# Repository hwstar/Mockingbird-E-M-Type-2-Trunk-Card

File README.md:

# Mockingbird-E-M-Type-2-Trunk-Card
An E&amp;M Type 2 trunk card for the Mockingbird Telephone Exchange

An interface card design for the Mockingbird Telephone Exchange. 

Features: 
* Provides one E&M type 2 interface
* STM32F103C8T6 microcontroller.
* Isolated local -48VDC supply for the M lead current
* Dry contacts for the E-lead
* Separate  RJ45 jacks for signalling and trunk pinouts.
* Uses standard 4 pair EIA568B Network cable pinout.
* Adjustable audio levels
* Accessed from the Main Microcontroller over I2C
* ATTEN signal to main microcontroller to tell it when there is an event to service.
* 4 Wire transformer isolated audio interface converts the balanced interface audio to unbalanced.
* Design in KiCAD 8.0.

The main project website is on hackaday.io here: https://hackaday.io/project/196044-mockingbird-telephone-exchange

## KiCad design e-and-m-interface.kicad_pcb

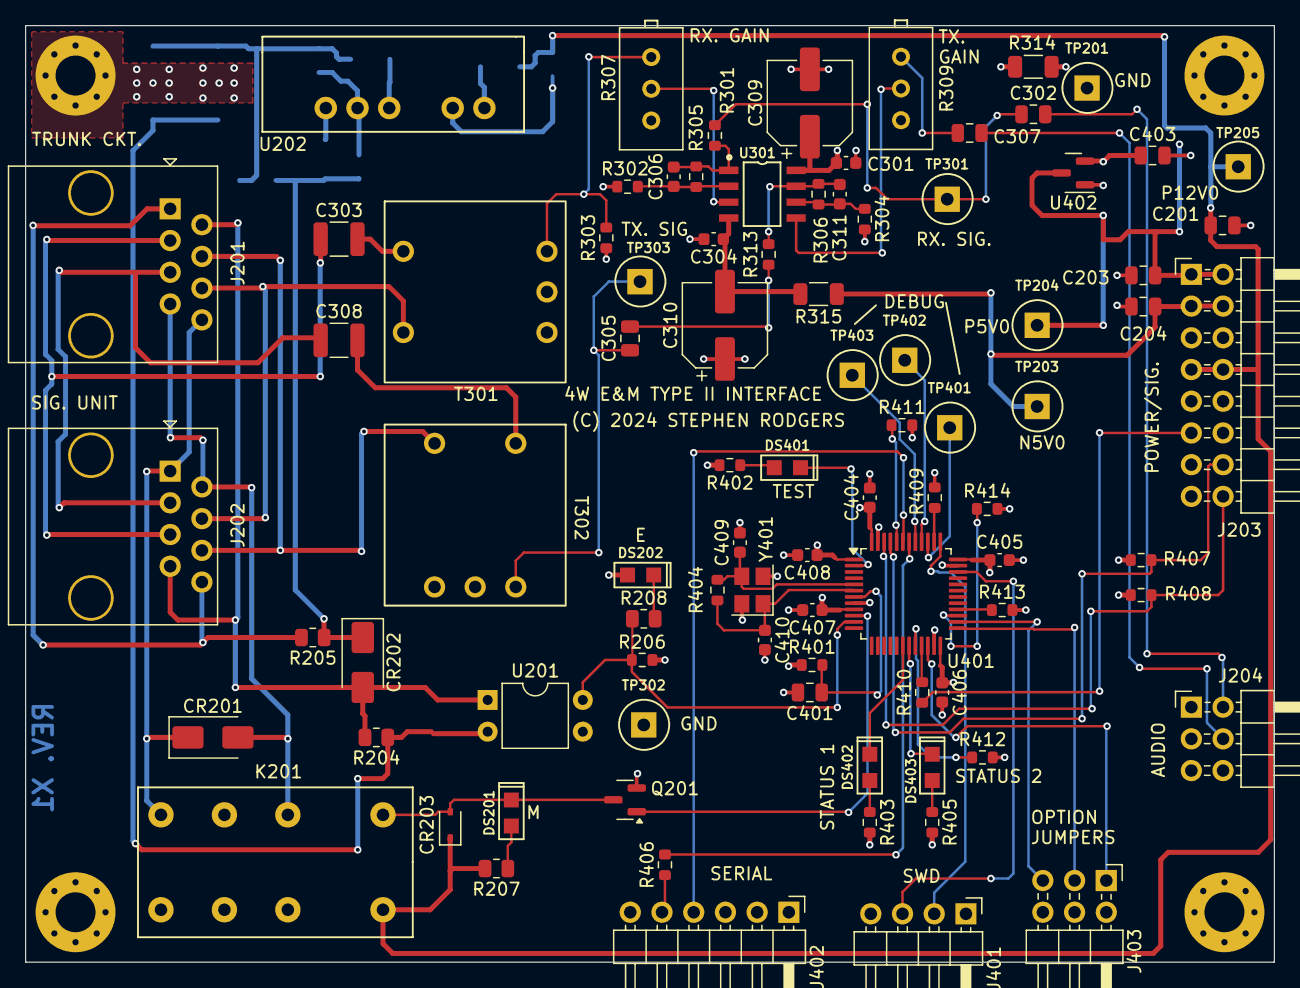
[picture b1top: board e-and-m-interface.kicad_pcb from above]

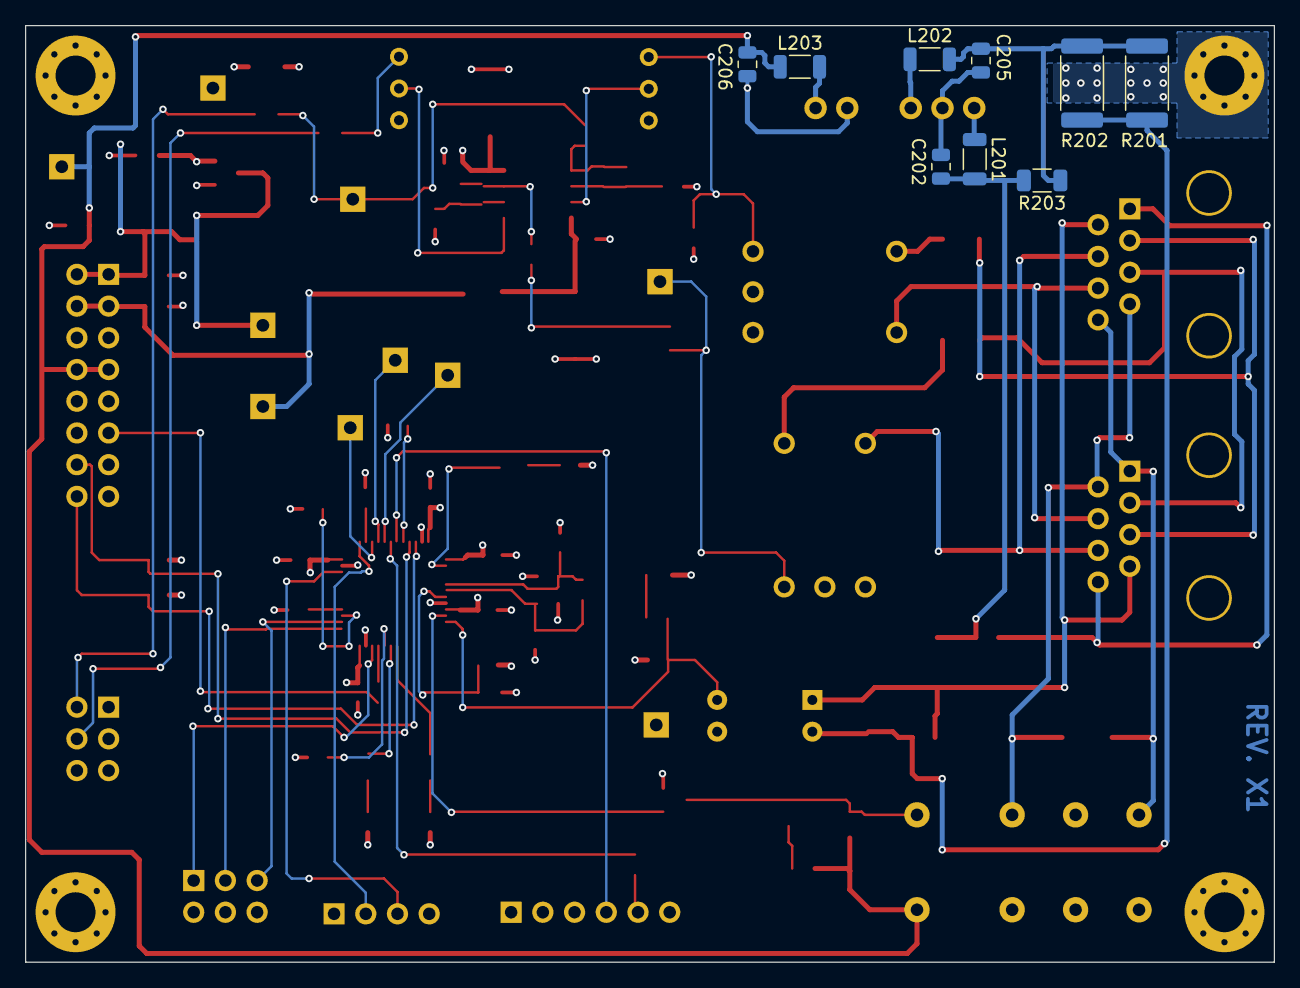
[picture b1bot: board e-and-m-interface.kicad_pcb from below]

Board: 4 copper layers, 100.0 x 75.0 mm, 101 parts (9 on the bottom side), 71 nets.

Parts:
C201, C203, C204: 10u; C_0805_2012Metric
C202, C205: 0.47u; C_0805_2012Metric
C206: 4.7u; C_0805_2012Metric
C301, C304, C404, C405, C406, C407, C408: 0.1u; C_0603_1608Metric
C302, C305, C307: 10U; C_0805_2012Metric
C303, C308: 3.3u; C_1210_3225Metric
C306, C311: 33p; C_0603_1608Metric
C309, C310: 100U; CP_Elec_6.3x7.7
C401: 1u; C_0805_2012Metric
C403: 22u; C_0805_2012Metric
C409, C410: 22p; C_0603_1608Metric
CR201, CR202: SMAJ64CA; D_SMA
CR203: 1N4148WS; D_SOD-323
DS201, DS202, DS401, DS402, DS403: LEDGRN-SAR; LED0805
J201, J202: RJ45; CONN_RJ45_HCTL_HC_RJ45_058_1_6
J203: Conn_02x08_Odd_Even; PinHeader_2x08_P2.54mm_Horizontal
J204, J403: Conn_02x03_Odd_Even; PinHeader_2x03_P2.54mm_Horizontal
J401: CONN4; PinHeader_1x04_P2.54mm_Horizontal
J402: CONN6; PinHeader_1x06_P2.54mm_Horizontal
K201: RELAY_2RT; RELAY-DPDT-HRS2H
L201, L202, L203: 4.7uH; L_1206_3216Metric
MH201, MH202, MH203, MH204: MountingHole_Pad; MountingHole_3.2mm_M3_Pad_Via
Q201: 2N7002; SOT-23
R201, R202: 4.7K; R_2512_6332Metric
R203: 12K; R_1206_3216Metric
R204, R208: 180; R_0805_2012Metric
R205: 0; R_0805_2012Metric
R206: 4.7K; R_0603_1608Metric
R207: 470; R_0805_2012Metric
R301, R410: 33; R_0603_1608Metric
R302, R304: 22K; R_0603_1608Metric
R303, R313: 620; R_0603_1608Metric
R305, R306: 100K; R_0603_1608Metric
R307, R309: 10K; Potentiometer_Bourns_3296X_Horizontal_Screw_SS
R314, R315: 10; R_1206_3216Metric
R401, R411, R412: 10K; R_0603_1608Metric
R402, R403, R405, R406: 470; R_0603_1608Metric
R404: 1M; R_0603_1608Metric
R407, R408: 2.2K; R_0603_1608Metric
R409, R413, R414: 0; R_0603_1608Metric
T301, T302: XFMR-AUDIO-COUPLING; XFMR_AUDIO_COUPLING_PP3.575_SPC_11_HOLE_0.85
TP201, TP203, TP204, TP205, TP301, TP302, TP303, TP401, TP402, TP403: TESTPINTPSQ025; TESTPIN
U201: EL817S1(B)(TU)-F; DIP-4_W7.62mm
U202: A1224S-1WR3
U301: LMC6482; SOIC8N-SAR
U401: STM32F103C8Tx; LQFP-48_7x7mm_P0.5mm
U402: ME6211A33M3G-N; SOT23-3-SAR-V2
Y401: 8.0M; Crystal_SMD_3225-4Pin_3.2x2.5mm

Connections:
/Top/ATTEN: J203.11, R410.1
/Top/Audio/N5V0_CLEAN: C304.1, C310.2, R315.2, U301.4 (V-)
/Top/Audio/P5V0_CLEAN: C301.2, C309.1, R314.2, U301.8 (V+)
/Top/Audio/RAP_TNV: C303.2, T301.1
/Top/Audio/XAP_TNV: C308.2, T302.1
/Top/Control/LEDN_TEST: DS401.2 (K), U401.2 (PC13)
/Top/Control/LED_STATUS_1_N: DS402.2 (K), U401.18 (PB0)
/Top/Control/LED_STATUS_2_N: DS403.2 (K), U401.19 (PB1)
/Top/Control/NRST: C401.1, R401.2, U401.7 (NRST)
/Top/Control/SW1: J403.1, U401.22 (PB11)
/Top/Control/SW2: J403.3, U401.25 (PB12)
/Top/Control/SW3: J403.5, U401.26 (PB13)
/Top/Control/SWCLK: J401.2, U401.37 (PA14)
/Top/Control/SWDIO: J401.3, U401.34 (PA13)
/Top/Control/TP1: TP401.1 (TP), U401.39 (PB3)
/Top/Control/TP2: TP402.1 (TP), U401.40 (PB4)
/Top/Control/TP3: TP403.1 (TP), U401.41 (PB5)
/Top/Control/UART_RX: J402.4, U401.43 (PB7)
/Top/Control/UART_TX: R406.2, U401.42 (PB6)
/Top/E_TNV: CR202.2 (A2), J201.2, J202.7, R204.2, U201.1
/Top/M_TNV: CR201.2 (A2), J201.7, J202.2, K201.12 (C2)
/Top/N5V0: C204.1, J203.3, J203.4, R315.1, TP203.1 (TP)
/Top/N48V0_RET_TNV: C202.1, CR202.1 (A1), L201.2, R203.2, R205.1
/Top/N48V0_TNV: C205.1, L202.2, R201.1, R202.1, R203.1
/Top/OPTO_LED_TNV: R201.2, R202.2, R204.1, U201.2
/Top/P3V3_CPU: C403.1, C404.1, C405.1, C406.1, C407.1, C408.1, DS202.1 (A), J401.4, R206.2, R401.1, R402.2, R403.2, R405.2, R407.1, R408.1, U401.1 (VBAT), U401.9 (VDDA), U401.24 (VDD), U401.36 (VDD), U401.48 (VDD), U402.2 (OUT)
/Top/P5V0: C203.1, J203.1, J203.2, R314.1, TP204.1 (TP), U402.3 (IN)
/Top/P12V0: C201.1, C206.1, CR203.1 (K), J203.7, J203.8, K201.8, L203.1, R207.2, TP205.1 (TP)
/Top/R1_TNV: J201.6, J202.4, T301.2
/Top/RXA: C302.2, J204.2
/Top/R_TNV: J201.4, J202.6, T302.2
/Top/SB_TNV: CR201.1 (A1), J201.8, J202.1, K201.16 (T2)
/Top/SCL: J203.14, R407.2, U401.45 (PB8)
/Top/SDA: J203.16, R408.2, U401.46 (PB9)
/Top/SEND_M: Q201.1 (G), U401.10 (PA0)
/Top/SENSE_E: R206.1, R208.1, U201.4, U401.11 (PA1)
/Top/SG_TNV: J201.1, J202.8, R205.2
/Top/T1_TNV: C303.1, J201.3, J202.5
/Top/TXA: C307.2, J204.4
/Top/T_TNV: C308.1, J201.5, J202.3
GND: C201.2, C203.2, C204.2, C206.2, C301.1, C304.2, C309.2, C310.1, C401.2, C403.2, C404.2, C405.2, C406.2, C407.2, C408.2, C409.2, C410.2, J203.9, J203.10, J203.12, J203.13, J203.15, J204.1, J204.3, J204.5, J204.6, J401.1, J402.1, J403.2, J403.4, J403.6, MH201.1, MH202.1, MH203.1, MH204.1, Q201.2 (S), R302.1, R303.1, R304.2, R307.1, R309.1, R409.2, R411.2, R412.2, R413.2, R414.2, T301.3, T302.3, TP201.1 (TP), TP302.1 (TP), U201.3, U202.2 (Vin-), U401.8 (VSSA), U401.23 (VSS), U401.35 (VSS), U401.47 (VSS), U402.1 (GND), Y401.2, Y401.4 (2)
unnamed: C305.2, R313.1
unnamed: C306.2, R301.1, R305.2, U301.1
unnamed: C307.1, R309.3
unnamed: C311.1, R306.1, R313.2, U301.7
unnamed: CR203.2 (A), DS201.2 (K), K201.9, Q201.3 (D)
unnamed: DS201.1 (A), R207.1
unnamed: DS202.2 (K), R208.2
unnamed: DS401.1 (A), R402.1
unnamed: DS402.1 (A), R403.1
unnamed: DS403.1 (A), R405.1
unnamed: J402.5, R406.1
unnamed: R303.2, R307.3, T301.5
unnamed: C305.1, T302.5, TP303.1 (TP)
unnamed: C302.1, R301.2, TP301.1 (TP)
unnamed: C202.2, C205.2, U202.5 (COM)
unnamed: L203.2, U202.1 (Vin+)
unnamed: L201.1, U202.6 (Vout+)
unnamed: L202.1, U202.4 (Vout-)
unnamed: R307.2, U301.3 (+)
unnamed: C306.1, R302.2, R305.1, U301.2 (-)
unnamed: R309.2, U301.5 (+)
unnamed: C311.2, R304.1, R306.2, U301.6 (-)
unnamed: R411.1, U401.44 (BOOT0)
unnamed: R409.1, U401.38 (PA15)
unnamed: R412.1, U401.20 (PB2)
unnamed: R410.2, U401.21 (PB10)
unnamed: R414.1, U401.27 (PB14)
unnamed: R413.1, U401.28 (PB15)
unnamed: C409.1, R404.1, U401.5 (PD0), Y401.3
unnamed: C410.1, R404.2, U401.6 (PD1), Y401.1

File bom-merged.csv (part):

Item,Part Number,Qty,Reference(s),Title/Description,Value on Schematic,Manufacturer,Manufacturer Part Number,Footprint
1,800003-106,6,"C201,C203,C204,C302,C305,C307","CAP,0805,10u,25V,X5R",10U,Murata Electronics,GRM21BR61E106KA73L,C_0805_2012Metric
1,800003-106,6,"C201,C203,C204,C302,C305,C307","CAP,0805,10u,25V,X5R",10U,Samsung Electromechanics,CL21A106KAYNNNE,C_0805_2012Metric
1,800003-106,6,"C201,C203,C204,C302,C305,C307","CAP,0805,10u,25V,X5R",10U,LCSC,C15850,C_0805_2012Metric
2,800423-474,2,"C202,C205","CAP,0805,0.47UF,50V,5%,X7R",0.47u,LCSC,C520080,C_0805_2012Metric
2,800423-474,2,"C202,C205","CAP,0805,0.47UF,50V,5%,X7R",0.47u,Yageo,CC0805JKX7R9BB474,C_0805_2012Metric
3,800003-475,1,C206,"CAP,0805,4.7u,25V,X5R",4.7u,Taiyo-Yuden,TMK212ABJ475KG-T,C_0805_2012Metric
3,800003-475,1,C206,"CAP,0805,4.7u,25V,X5R",4.7u,LCSC,"C1779,C386082",C_0805_2012Metric
3,800003-475,1,C206,"CAP,0805,4.7u,25V,X5R",4.7u,Samsung Electromechanics,CL21A475KAQNNNE,C_0805_2012Metric
4,800063-104,7,"C301,C304,C404-C408","CAP,0603,0.1u,50V,X7R",0.1u,Kyocera AVX,06035C104KAT2A,C_0603_1608Metric
4,800063-104,7,"C301,C304,C404-C408","CAP,0603,0.1u,50V,X7R",0.1u,Yageo,CC0603KRX7R9BB104,C_0603_1608Metric
4,800063-104,7,"C301,C304,C404-C408","CAP,0603,0.1u,50V,X7R",0.1u,LCSC,C14663,C_0603_1608Metric
5,800428-335,2,"C303,C308","CAP,1210,3.3UF,10%,100V,X7R",3.3u,LCSC,C692313,C_1210_3225Metric
5,800428-335,2,"C303,C308","CAP,1210,3.3UF,10%,100V,X7R",3.3u,Prosperity Dielectrics,FS32X335K101EGG,C_1210_3225Metric
6,800002-330,2,"C306,C311","CAP,0603,33p,50V,C0G",33p,Samsung Electromechanics,CL10C330JB8NNNC,C_0603_1608Metric
6,800002-330,2,"C306,C311","CAP,0603,33p,50V,C0G",33p,LCSC,C1663,C_0603_1608Metric
7,800421-107,2,"C309,C310","CAP,ALUM_ELECT,100uF,35V,ESR 600mOHM,6.3MM,2000 HR",100U,LCSC,C2836437,CP_Elec_6.3x7.7
7,800421-107,2,"C309,C310","CAP,ALUM_ELECT,100uF,35V,ESR 600mOHM,6.3MM,2000 HR",100U,KNSCHA,RVE100UF35V67RV0072,CP_Elec_6.3x7.7
8,800238-105,1,C401,"CAP,0805,1u,50V,X7R",1u,WALSIN TECH CORP,0805B105K500CT,C_0805_2012Metric
8,800238-105,1,C401,"CAP,0805,1u,50V,X7R",1u,Samsung Electromechanics,CL21B105KBFNNNE,C_0805_2012Metric
8,800238-105,1,C401,"CAP,0805,1u,50V,X7R",1u,LCSC,C28323,C_0805_2012Metric
9,800003-226,1,C403,"CAP,0805,22u,25V,X5R",22u,LCSC,C45783,C_0805_2012Metric
9,800003-226,1,C403,"CAP,0805,22u,25V,X5R",22u,Samsung Electromechanics,CL21A226MAQNNNE,C_0805_2012Metric
10,800002-220,2,"C409,C410","CAP,0603,22p,50V,C0G",22p,LCSC,C1653,C_0603_1608Metric
10,800002-220,2,"C409,C410","CAP,0603,22p,50V,C0G",22p,Samsung Electromechanics,CL10C220JB8NNNC,C_0603_1608Metric
11,800335-064,2,"CR201,CR202","DIODE,TVS,64V,BIDIRECT,SMA",SMAJ64CA,LCSC,C2898428,D_SMA
11,800335-064,2,"CR201,CR202","DIODE,TVS,64V,BIDIRECT,SMA",SMAJ64CA,YFW,SMAJ64CA,D_SMA
12,800264-102,1,CR203,"DIODE,SWITCHING,75V,SOD-323",1N4148WS,LCSC,C2128,D_SOD-323
12,800264-102,1,CR203,"DIODE,SWITCHING,75V,SOD-323",1N4148WS,JIANGSU CHANGJIANG ELECTRONICS TECHNOLOGY CO LTD.,1N4148WS,D_SOD-323
13,800113-102,5,"DS201,DS202,DS401-DS403","LED,GREEN,0805",LEDGRN-SAR,LCSC,C434435,LED0805
13,800113-102,5,"DS201,DS202,DS401-DS403","LED,GREEN,0805",LEDGRN-SAR,Yongsu Photoelectric,SZYY0805YG,LED0805
14,800429-101,2,"J201,J202","CONN,JACK,MODULAR,8P8C,PLASTIC,PTH",RJ45,LCSC,C3000197,CONN_RJ45_HCTL_HC_RJ45_058_1_6
14,800429-101,2,"J201,J202","CONN,JACK,MODULAR,8P8C,PLASTIC,PTH",RJ45,HCTL,HC-RJ45-058-1-6,CONN_RJ45_HCTL_HC_RJ45_058_1_6
15,800343-102,1,J203,"CONN,HDR,2 POS.,STR,PTH,2.54MM,TIN",Conn_02x08_Odd_Even,DEALON,DZ254R-11-02-63,PinHeader_2x08_P2.54mm_Horizontal
15,800343-102,1,J203,"CONN,HDR,2 POS.,STR,PTH,2.54MM,TIN",Conn_02x08_Odd_Even,LCSC,C2935908,PinHeader_2x08_P2.54mm_Horizontal
16,800425-106,2,"J204,J403","CONN,HDR,STRIP,DUAL ROW,RA,PTH,2X3,0.254 MM PITCH",Conn_02x03_Odd_Even,LCSC,C2935935,PinHeader_2x03_P2.54mm_Horizontal
16,800425-106,2,"J204,J403","CONN,HDR,STRIP,DUAL ROW,RA,PTH,2X3,0.254 MM PITCH",Conn_02x03_Odd_Even,DEALON,DZ254W-22-06-69,PinHeader_2x03_P2.54mm_Horizontal
17,800383-104,1,J401,"HEADER,STRIP,RA,4 POS,0.254MM PITCH",CONN4,DEALON,DZ254W-11-04-65,PinHeader_1x04_P2.54mm_Horizontal
17,800383-104,1,J401,"HEADER,STRIP,RA,4 POS,0.254MM PITCH",CONN4,LCSC,C2935929,PinHeader_1x04_P2.54mm_Horizontal
18,800383-106,1,J402,"HEADER,STRIP,RA,6 POS,0.254MM PITCH",CONN6,LCSC,C2935931,PinHeader_1x06_P2.54mm_Horizontal
18,800383-106,1,J402,"HEADER,STRIP,RA,6 POS,0.254MM PITCH",CONN6,DEALON,DZ254W-11-06-65,PinHeader_1x06_P2.54mm_Horizontal
19,800279-012,1,K201,"RELAY, TELECOM, DIP, DPDT, 12V",RELAY_2RT,HUIGANG,HRS2H-S-DC12V-N,RELAY-DPDT-HRS2H
19,800279-012,1,K201,"RELAY, TELECOM, DIP, DPDT, 12V",RELAY_2RT,LCSC,C60087,RELAY-DPDT-HRS2H
20,800441-047,3,L201-L203,"IND,1206,4.7UH,0.7A,+/-20%",4.7uH,FH (Guangdong Fenghua Advanced Tech),CMP321609UD4R7MT,L_1206_3216Metric
20,800441-047,3,L201-L203,"IND,1206,4.7UH,0.7A,+/-20%",4.7uH,LCSC,C139250,L_1206_3216Metric
21,800346-101,1,Q201,"XSTR,MOSFET,SOT-23,N-CH,60V,115MA",2N7002,LCSC,C8545,SOT-23
21,800346-101,1,Q201,"XSTR,MOSFET,SOT-23,N-CH,60V,115MA",2N7002,JIANGSU CHANGJIANG ELECTRONICS TECHNOLOGY CO LTD.,2N7002,SOT-23
22,800248-472,2,"R201,R202","RES,2512,4.7K OHM, 1%,1W",4.7K,LCSC,C473645,R_2512_6332Metric
22,800248-472,2,"R201,R202","RES,2512,4.7K OHM, 1%,1W",4.7K,Uni-Royal,25121WF4701T4E,R_2512_6332Metric
23,800057-123,1,R203,"RES,1206,12K OHM,1%,1/4W",12K,LCSC,C965064,R_1206_3216Metric
23,800057-123,1,R203,"RES,1206,12K OHM,1%,1/4W",12K,Uni-Royal,NQ06W4F1202T5E,R_1206_3216Metric
24,800235-181,2,"R204,R208","RES,0805,180,1%",180,Uni-Royal,0805W8F1800T5E,R_0805_2012Metric
24,800235-181,2,"R204,R208","RES,0805,180,1%",180,LCSC,C25270,R_0805_2012Metric
25,800235-000,1,R205,"RES,0805,0,1%",0,LCSC,C17477,R_0805_2012Metric
25,800235-000,1,R205,"RES,0805,0,1%",0,Uni-Royal,0805W8F0000T5E,R_0805_2012Metric
26,800022-470,1,R206,"RES,0603,4.70K OHM,1%,E24",4.7K,Resistor.Today,AECR0603F4K70K9,R_0603_1608Metric
26,800022-470,1,R206,"RES,0603,4.70K OHM,1%,E24",4.7K,Uni-Royal,0603WAF4701T5E,R_0603_1608Metric
26,800022-470,1,R206,"RES,0603,4.70K OHM,1%,E24",4.7K,LCSC,"C23162,C328364",R_0603_1608Metric
27,800235-471,1,R207,"RES,0805,470,1%",470,LCSC,C17710,R_0805_2012Metric
27,800235-471,1,R207,"RES,0805,470,1%",470,Uni-Royal,0805W8F4700T5E,R_0805_2012Metric
28,800020-330,2,"R301,R410","RES,0603,33 OHM,1%,E24",33,Uni-Royal,0603WAF330JT5E,R_0603_1608Metric
28,800020-330,2,"R301,R410","RES,0603,33 OHM,1%,E24",33,LCSC,C23140,R_0603_1608Metric
29,800023-220,2,"R302,R304","RES,0603,22K OHM,1%",22K,LCSC,C31850,R_0603_1608Metric
29,800023-220,2,"R302,R304","RES,0603,22K OHM,1%",22K,Uni-Royal,0603WAF2202T5E,R_0603_1608Metric
30,800021-620,2,"R303,R313","RES,0603,620 OHM,1%,E24",620,LCSC,C23220,R_0603_1608Metric
30,800021-620,2,"R303,R313","RES,0603,620 OHM,1%,E24",620,Uni-Royal,0603WAF6200T5E,R_0603_1608Metric
31,800024-100,2,"R305,R306","RES,0603,100K OHM,1%,E24",100K,LCSC,C25803,R_0603_1608Metric
31,800024-100,2,"R305,R306","RES,0603,100K OHM,1%,E24",100K,Uni-Royal,0603WAF1003T5E,R_0603_1608Metric
32,800430-103,2,"R307,R309","RES,TRIMMER,3296,HORIZ,PTH,10K,10%,0.5W",10K,BOCHEN,3296X-1-103,Potentiometer_Bourns_3296X_Horizontal_Screw_SS
32,800430-103,2,"R307,R309","RES,TRIMMER,3296,HORIZ,PTH,10K,10%,0.5W",10K,LCSC,C118955,Potentiometer_Bourns_3296X_Horizontal_Screw_SS
33,800057-100,2,"R314,R315","RES,1206,10 OHM,1%,1/4W",10,LCSC,C844016,R_1206_3216Metric
33,800057-100,2,"R314,R315","RES,1206,10 OHM,1%,1/4W",10,Vishay,CRCW120610R0FKEB,R_1206_3216Metric
34,800023-100,3,"R401,R411,R412","RES,0603,10.0K OHM,1%",10K,WALSIN TECH CORP,MR06X1002FTL,R_0603_1608Metric
34,800023-100,3,"R401,R411,R412","RES,0603,10.0K OHM,1%",10K,Uni-Royal,0603WAF1002T5E,R_0603_1608Metric
34,800023-100,3,"R401,R411,R412","RES,0603,10.0K OHM,1%",10K,LCSC,C25804,R_0603_1608Metric
35,800021-470,4,"R402,R403,R405,R406","RES,0603,470 OHM,1%,E24",470,LCSC,"C23179
",R_0603_1608Metric
35,800021-470,4,"R402,R403,R405,R406","RES,0603,470 OHM,1%,E24",470,Uni-Royal,0603WAF4700T5E,R_0603_1608Metric
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
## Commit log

2024-05-15 Initial commit at rev A
2024-05-15 Exclude .lck
2024-05-16 Update README, add photo

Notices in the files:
e-and-m-interface.kicad_pcb:
(C) 2024 STEPHEN RODGERS
